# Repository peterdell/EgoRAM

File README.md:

# EgoRAM

The Atari 8-bit RAM cartridge with its own ego and opinion on what should be in the RAM.

$D500-$D5FF
===========

| Address | Name | Description Read | Write |
|---------+------+------------|
| $D500   |      | 'E'        |
| $D501   |      | 'R'        |
| $D502   |      | 'A'        |
| $D503   |      | 'M'        |
| $D504   |      | $YY        |
| $D505   |      | $YY        |
| $D506   |      | $MM        |
| $D507   |      | $DD        |

| $D508   |  ECTL  | $00=ready, $01=busy, $8x=error  | $00=reset,$01=begin command |
| $D509   |  EDAT  | Data, increments address        | Data to write, increments address |
| $dD0a   |  ERET  | n/a                             | Strobe, run command |

| Command | Name     | Arguments | Description 
| G       | Graphics | mode: byte (8,9,15), address: word ($8000...$bffff), width: byte (bytes 32,40,48), height: byte (lines 1..255) | width*height<$2000
| SD      | Shape Define | shapeNumber: word ($0001-$ffff), bpp: ($01, $02, $04), width: word (pixels 1..256), height: word (pixels 1..256), format: byte ($01=raw), paletteSize: word, paletteMap: array[paletteSize], maskIndex: byte (0..paletteSize), data: array[0...dataSize-1] | dataSize = 

[Getting started with Raspberry Pi
Pico-series](https://pip-assets.raspberrypi.com/categories/610-raspberry-pi-pico/documents/RP-008276-DS-1-getting-started-with-pico.pdf)
If you get an error message "No accessible RP2040/RP2350 devices in BOOTSEL mode were found." accompanied by a note similar to Device at bus 1, address 7 appears to an RP2040 device in BOOTSEL mode, but picotool was unable to connect, indicating that there was a Pico-series device connected, then you can run picotool using sudo, e.g.
$ sudo picotool info -a
If you get this message on Windows, you will need to install a driver. Download and run [Zadig](https://zadig.akeo.ie/), select RP2 Boot (Interface 1) from the dropdown box, select WinUSB as the driver, and click the "Install Driver" button. Wait for the installation to complete - this may take a few minutes.

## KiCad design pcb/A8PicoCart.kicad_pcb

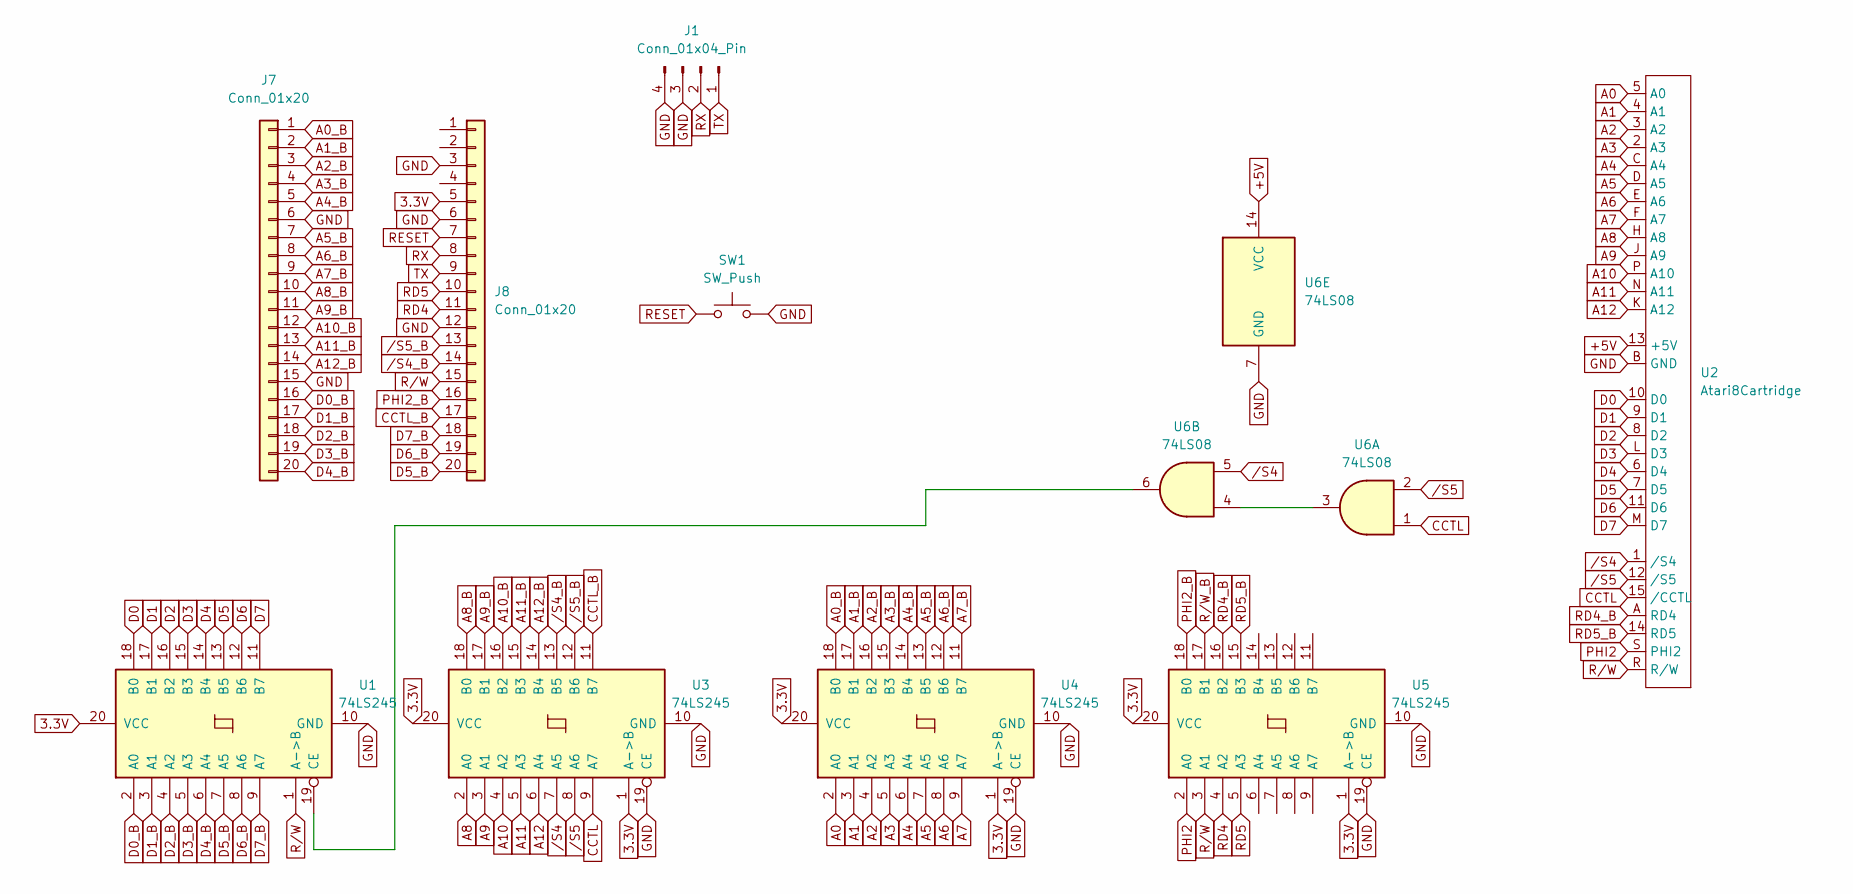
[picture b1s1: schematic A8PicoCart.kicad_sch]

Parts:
J1: Conn_01x04_Pin; PinHeader_1x04_P2.54mm_Horizontal
J7, J8: Conn_01x20; PinSocket_1x20_P2.54mm_Vertical
SW1: SW_Push; SW_PUSH_6mm_H8mm
U1, U3, U4, U5: 74LS245; DIP-20_W7.62mm_Socket_LongPads
U2: Atari8Cartridge; Atari8Cartridge MountHoles (taller)
U6: 74LS08; DIP-14_W7.62mm_LongPads

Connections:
3.3V: J8.5, U1.20 (VCC), U3.1 (A->B), U3.20 (VCC), U4.1 (A->B), U4.20 (VCC), U5.1 (A->B), U5.20 (VCC)
+5V: U2.13 (+5V), U6.14 (VCC)
A0: U2.5 (A0), U4.2 (A0)
A0_B: J7.1, U4.18 (B0)
A1: U2.4 (A1), U4.3 (A1)
A1_B: J7.2, U4.17 (B1)
A2: U2.3 (A2), U4.4 (A2)
A2_B: J7.3, U4.16 (B2)
A3: U2.2 (A3), U4.5 (A3)
A3_B: J7.4, U4.15 (B3)
A4: U2.C (A4), U4.6 (A4)
A4_B: J7.5, U4.14 (B4)
A5: U2.D (A5), U4.7 (A5)
A5_B: J7.7, U4.13 (B5)
A6: U2.E (A6), U4.8 (A6)
A6_B: J7.8, U4.12 (B6)
A7: U2.F (A7), U4.9 (A7)
A7_B: J7.9, U4.11 (B7)
A8: U2.H (A8), U3.2 (A0)
A8_B: J7.10, U3.18 (B0)
A9: U2.J (A9), U3.3 (A1)
A9_B: J7.11, U3.17 (B1)
A10: U2.P (A10), U3.4 (A2)
A10_B: J7.12, U3.16 (B2)
A11: U2.N (A11), U3.5 (A3)
A11_B: J7.13, U3.15 (B3)
A12: U2.K (A12), U3.6 (A4)
A12_B: J7.14, U3.14 (B4)
CCTL: U2.15 (/CCTL), U3.9 (A7), U6.1
CCTL_B: J8.17, U3.11 (B7)
D0: U1.18 (B0), U2.10 (D0)
D0_B: J7.16, U1.2 (A0)
D1: U1.17 (B1), U2.9 (D1)
D1_B: J7.17, U1.3 (A1)
D2: U1.16 (B2), U2.8 (D2)
D2_B: J7.18, U1.4 (A2)
D3: U1.15 (B3), U2.L (D3)
D3_B: J7.19, U1.5 (A3)
D4: U1.14 (B4), U2.6 (D4)
D4_B: J7.20, U1.6 (A4)
D5: U1.13 (B5), U2.7 (D5)
D5_B: J8.20, U1.7 (A5)
D6: U1.12 (B6), U2.11 (D6)
D6_B: J8.19, U1.8 (A6)
D7: U1.11 (B7), U2.M (D7)
D7_B: J8.18, U1.9 (A7)
GND: J1.3, J1.4, J7.6, J7.15, J8.3, J8.6, J8.12, SW1.2, U1.10 (GND), U2.B (GND), U3.10 (GND), U3.19 (CE), U4.10 (GND), U4.19 (CE), U5.10 (GND), U5.19 (CE), U6.7 (GND)
unnamed: U1.19 (CE), U6.6
unnamed: U6.3, U6.4
PHI2: U2.S (PHI2), U5.2 (A0)
PHI2_B: J8.16, U5.18 (B0)
RD4: J8.11, U5.4 (A2)
RD4_B: U2.A (RD4), U5.16 (B2)
RD5: J8.10, U5.5 (A3)
RD5_B: U2.14 (RD5), U5.15 (B3)
RESET: J8.7, SW1.1
RX: J1.2, J8.8
R/W: J8.15, U1.1 (A->B), U2.R (R/W), U5.3 (A1)
R/W_B: U5.17 (B1)
TX: J1.1, J8.9
/S4: U2.1 (/S4), U3.7 (A5), U6.5
/S4_B: J8.14, U3.13 (B5)
/S5: U2.12 (/S5), U3.8 (A6), U6.2
/S5_B: J8.13, U3.12 (B6)

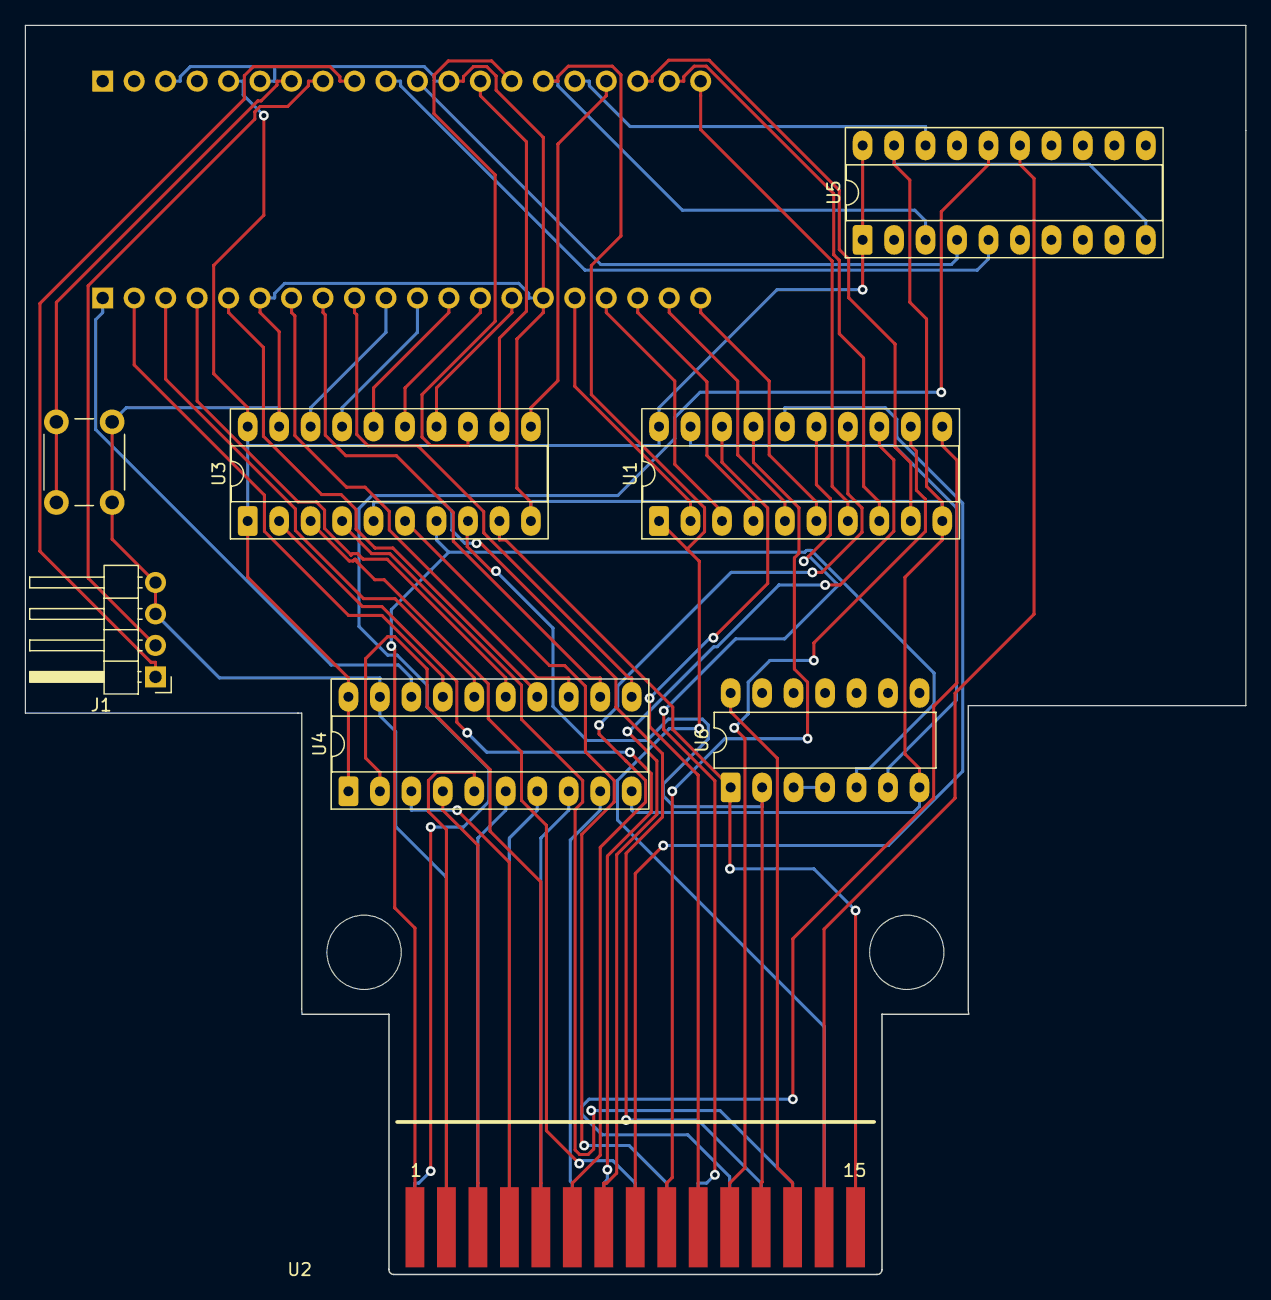
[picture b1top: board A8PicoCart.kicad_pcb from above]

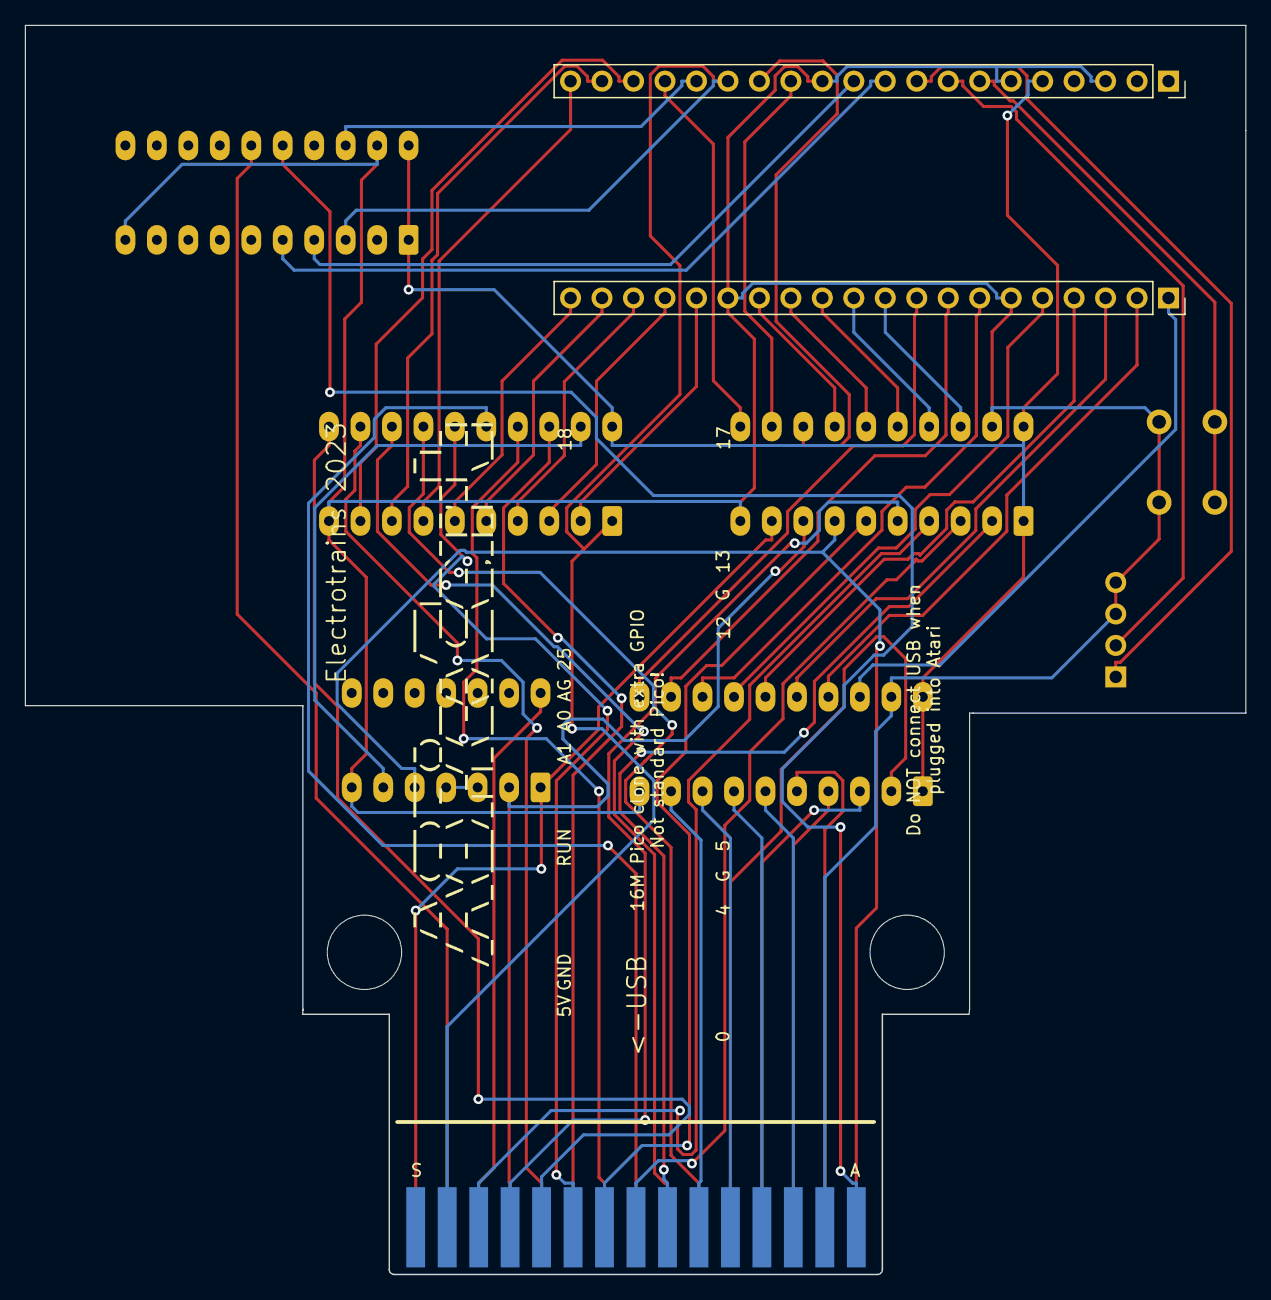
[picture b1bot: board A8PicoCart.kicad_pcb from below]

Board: 2 copper layers, 98.5 x 100.8 mm, 10 parts (2 on the bottom side), 63 nets.

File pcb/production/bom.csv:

Designator,Footprint,Quantity,Value,LCSC Part #
J1,PinHeader_1x04_P2.54mm_Horizontal,1,Conn_01x04_Pin,
"J7, J8",PinSocket_1x20_P2.54mm_Vertical,2,Conn_01x20,
SW1,SW_PUSH_6mm_H8mm,1,SW_Push,
"U1, U3, U4, U5",DIP-20_W7.62mm_Socket_LongPads,4,74LS245,
U2,Atari8Cartridge MountHoles (taller),1,Atari8Cartridge,
U6,DIP-14_W7.62mm_LongPads,1,74LS08,

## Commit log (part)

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2026-06-06 rename to EgoRAM
2026-06-06 refactoring & busy bit
2026-06-06 Atari Build
2026-06-08 first commands working
2026-06-10 do not use
2026-06-10 bouncing bounds improved
2026-06-12 write to d5xx fixed
2026-06-14 intrumentation
2026-06-24 masking with 2bpp, 4bpp should also work - not tested
2026-06-26 Structure system equates
2026-06-26 charset implemented
